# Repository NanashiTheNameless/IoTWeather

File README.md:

# IoTWeather

Simple IotWeather stuff, Released As-Is no support of any kind

## Support My Work

If this project is useful to you, you can support it here:

- [<https://github.com/sponsors/NanashiTheNameless>](<https://github.com/sponsors/NanashiTheNameless>)
- [<https://buymeacoffee.com/NamelessNanashi>](<https://buymeacoffee.com/NamelessNanashi>)
- [<https://ko-fi.com/NanashiTheNameless>](<https://ko-fi.com/NanashiTheNameless>)
- [<https://liberapay.com/NamelessNanashi>](<https://liberapay.com/NamelessNanashi>)
- [<https://throne.com/NamelessNanashi>](<https://throne.com/NamelessNanashi>)

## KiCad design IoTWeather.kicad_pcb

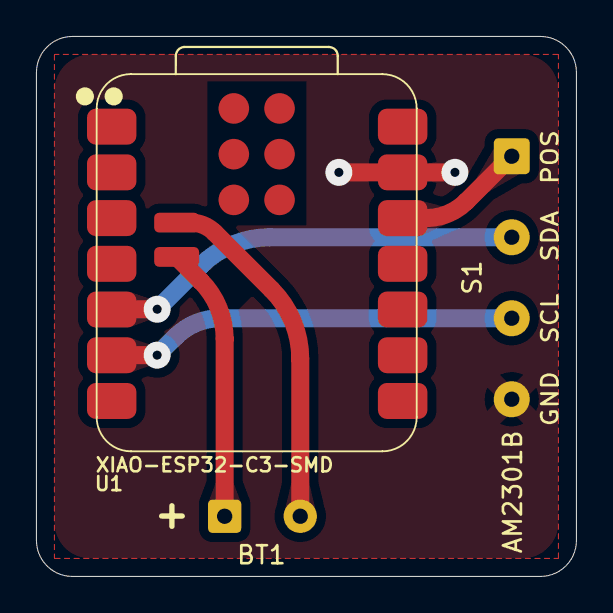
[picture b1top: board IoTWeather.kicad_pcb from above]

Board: 2 copper layers, 30.0 x 30.0 mm, 3 parts (0 on the bottom side), 6 nets.

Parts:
BT1: Battery_Cell; SolderWire-0.25sqmm_1x02_P4.2mm_D0.65mm_OD1.7mm
S1: AM2301B; SolderWire-0.25sqmm_1x04_P4.5mm_D0.65mm_OD2mm
U1: XIAO-ESP32-C3-SMD

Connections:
+3.3V: S1.1, U1.12 (3V3)
GND: S1.4, U1.13 (GND)
unnamed: BT1.1 (+), U1.15 (BAT)
unnamed: BT1.2 (-), U1.16 (GND)
unnamed: S1.2, U1.5 (PA8_A4_D4_SDA)
unnamed: S1.3, U1.6 (PA9_A5_D5_SCL)

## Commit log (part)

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2025-01-24 fix typo
2025-01-24 Add license
2025-01-24 add first version
2025-01-24 [ImgBot] Optimize images
    *Total -- 264.03kb -> 229.45kb (13.1%)
    /Wiring Diagragm.png -- 64.28kb -> 47.46kb (26.17%)
    /Code/Wiring Diagragm.png -- 64.28kb -> 47.46kb (26.17%)
    /Code/pin_map.png -- 135.47kb -> 134.53kb (0.69%)
2025-10-29 Update license to version 1.3 with corrections
2026-01-25 Change license to version 1.3
    Updated license information in the HTML file.
2026-02-17 Update license references to version 1.3 across all relevant files
2026-02-17 Update KiCad files
2026-05-17 Add funding options to FUNDING.yml

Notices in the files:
IoTWeather.kicad_pcb:
Copyright: NamelessNanashi
